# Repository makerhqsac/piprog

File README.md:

# piprog
PiProg - Raspberry Pi EEPROM and ICSP Programmer HAT

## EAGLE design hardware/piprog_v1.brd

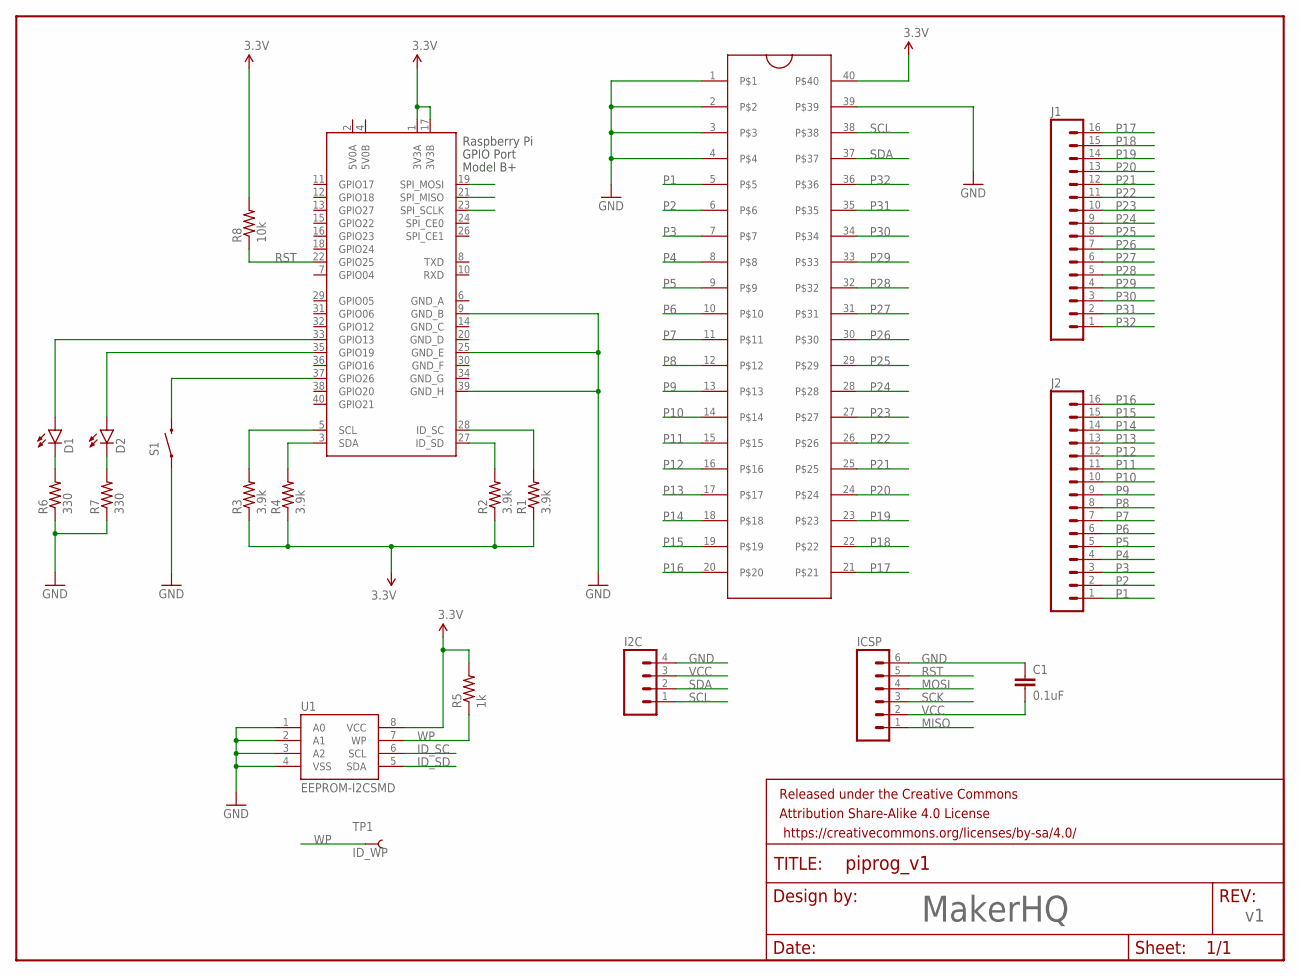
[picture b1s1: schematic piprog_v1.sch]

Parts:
C1: 0.1uF; CAP-PTH-SMALL
D1, D2: LED3MM
FRAME1: FRAME-LETTERNO_PACKAGE; DUMMY
I2C: M04PTH; 1X04
ICSP: M06SILK_FEMALE_PTH; 1X06
J1, J2: M16PTH; 1X16
R1, R2, R3, R4: 3.9k; AXIAL-0.4
R5: 1k; AXIAL-0.4
R6, R7: 330; AXIAL-0.4
R8: 10k; AXIAL-0.4
S1: SWITCH-MOMENTARY-2PTH; TACTILE-PTH
TP1: ID_WP; PAD.03X.04
U1: EEPROM-I2CSMD; SO08
U$2: ZIFSOCKET-40-6DIL40-6-ZIF_SOCKET; DIL40-6-ZIF_SOCKET
X1: RASPI_BOARD_B+#_HD; RASPI_BOARD_B+HAT_DF

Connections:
5V0A: X1.2 (5V0A)
5V0B: X1.4 (5V0B)
GND: C1.1, I2C.4, ICSP.6, R6.P$1 (1), R7.P$1 (1), S1.1, U1.1 (A0), U1.2 (A1), U1.3 (A2), U1.4 (VSS), U$2.1, U$2.2, U$2.3, U$2.4, U$2.39, X1.9 (GND_B), X1.25 (GND_E), X1.39 (GND_H)
GND_A: X1.6 (GND_A)
GND_C: X1.14 (GND_C)
GND_D: X1.20 (GND_D)
GND_F: X1.30 (GND_F)
GND_G: X1.34 (GND_G)
ID_SC: R1.P$2 (2), U1.6 (SCL), X1.28 (ID_SC)
ID_SD: R2.P$2 (2), U1.5 (SDA), X1.27 (ID_SD)
MISO: ICSP.1, X1.21 (SPI_MISO)
MOSI: ICSP.4, X1.19 (SPI_MOSI)
unnamed: D2.K (C), R7.P$2 (2)
unnamed: D1.K (C), R6.P$2 (2)
unnamed: D1.A, X1.33 (GPIO13)
unnamed: D2.A, X1.35 (GPIO19)
unnamed: S1.3 (2), X1.37 (GPIO26)
P1: J2.1, U$2.5
P2: J2.2, U$2.6
P3: J2.3, U$2.7
P4: J2.4, U$2.8
P5: J2.5, U$2.9
P6: J2.6, U$2.10
P7: J2.7, U$2.11
P8: J2.8, U$2.12
P9: J2.9, U$2.13
P10: J2.10, U$2.14
P11: J2.11, U$2.15
P12: J2.12, U$2.16
P13: J2.13, U$2.17
P14: J2.14, U$2.18
P15: J2.15, U$2.19
P16: J2.16, U$2.20
P17: J1.16, U$2.21
P18: J1.15, U$2.22
P19: J1.14, U$2.23
P20: J1.13, U$2.24
P21: J1.12, U$2.25
P22: J1.11, U$2.26
P23: J1.10, U$2.27
P24: J1.9, U$2.28
P25: J1.8, U$2.29
P26: J1.7, U$2.30
P27: J1.6, U$2.31
P28: J1.5, U$2.32
P29: J1.4, U$2.33
P30: J1.3, U$2.34
P31: J1.2, U$2.35
P32: J1.1, U$2.36
RST: ICSP.5, R8.P$1 (1), X1.22 (GPIO25)
SCK: ICSP.3, X1.23 (SPI_SCLK)
SCL: I2C.1, R3.P$2 (2), U$2.38, X1.5 (SCL)
SDA: I2C.2, R4.P$2 (2), U$2.37, X1.3 (SDA)
VCC: C1.2, I2C.3, ICSP.2, R1.P$1 (1), R2.P$1 (1), R3.P$1 (1), R4.P$1 (1), R5.P$2 (2), R8.P$2 (2), U1.8 (VCC), U$2.40, X1.1 (3V3A), X1.17 (3V3B)
WP: R5.P$1 (1), TP1.P$1, U1.7 (WP)

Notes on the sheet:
MakerHQ

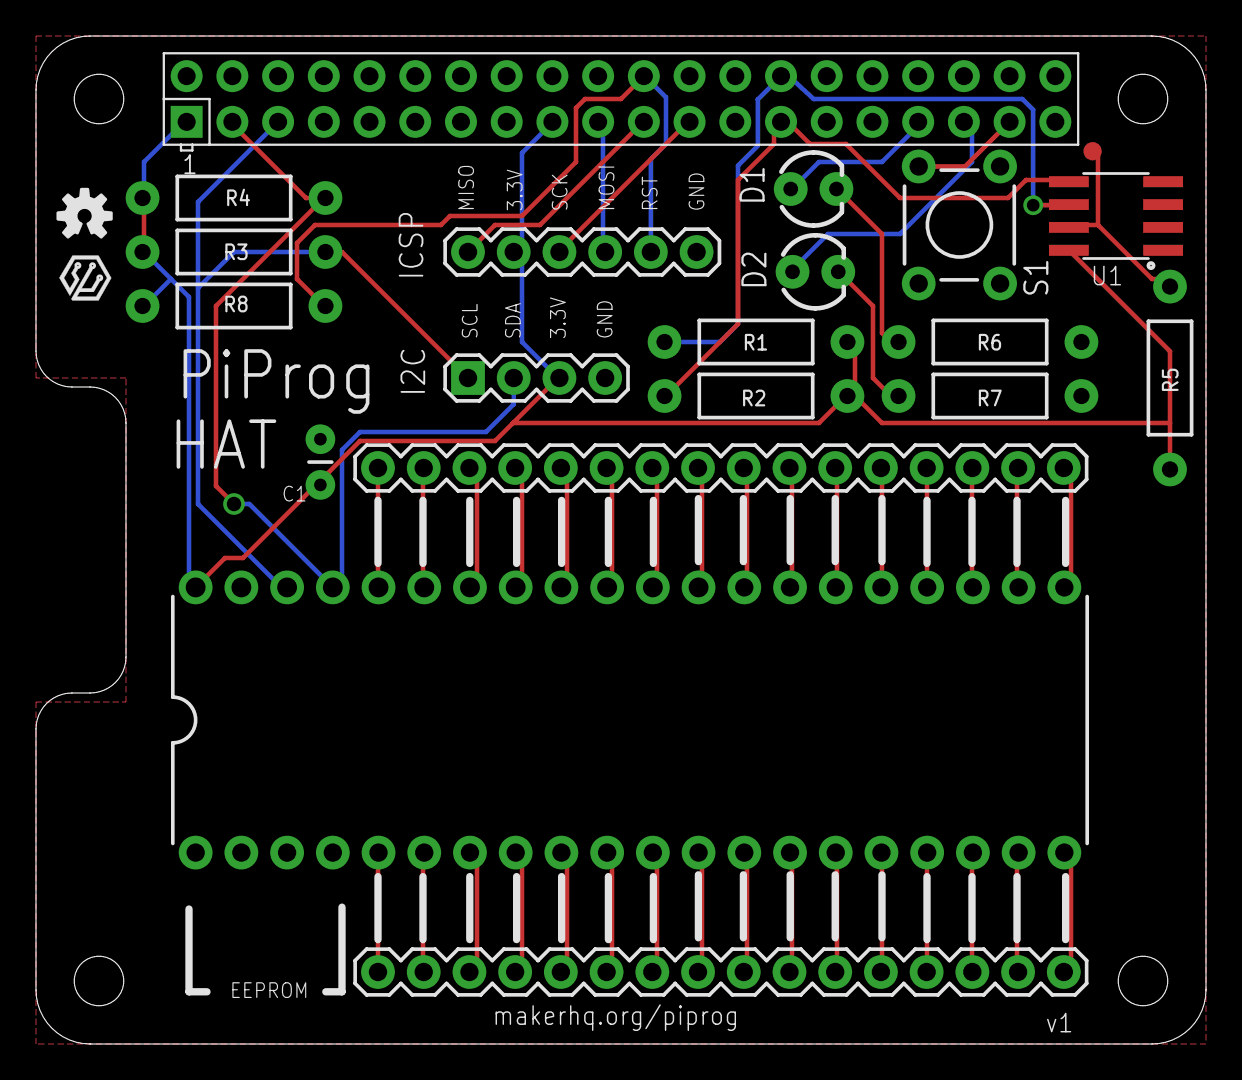
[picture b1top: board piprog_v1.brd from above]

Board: 2 copper layers, 65.0 x 56.0 mm, 23 parts (0 on the bottom side), 48 nets.

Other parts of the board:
U$1: OSHW-LOGO-S
U$3: MAKERHQ_LOGO_S

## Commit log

2016-10-26 Initial files
2016-10-26 Working eeprom writer
2016-10-28 icsp programmer almost done
2016-10-28 working code
2016-10-28 changed reset pin, add reset pullup
2016-10-31 Set fuses after flashing, if fuse settings are present
2016-11-18 Add utility to write hat eeproms using eepmake to generate unique eeprom per invocation
2016-11-18 Fix hat write utility
2017-04-18 add assembly images
2017-04-22 image update

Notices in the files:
parts and their libraries:
SparkFun-Connectors: Licensing: Creative Commons ShareAlike 4.0 International - https://creativecommons.org/licenses/by-sa/4.0
SparkFun-Aesthetics: Released under the Creative Commons Attribution Share-Alike 4.0 License
SparkFun-Aesthetics: https://creativecommons.org/licenses/by-sa/4.0
